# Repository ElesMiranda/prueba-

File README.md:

# prueba-
preuba del uso de kicad y Github

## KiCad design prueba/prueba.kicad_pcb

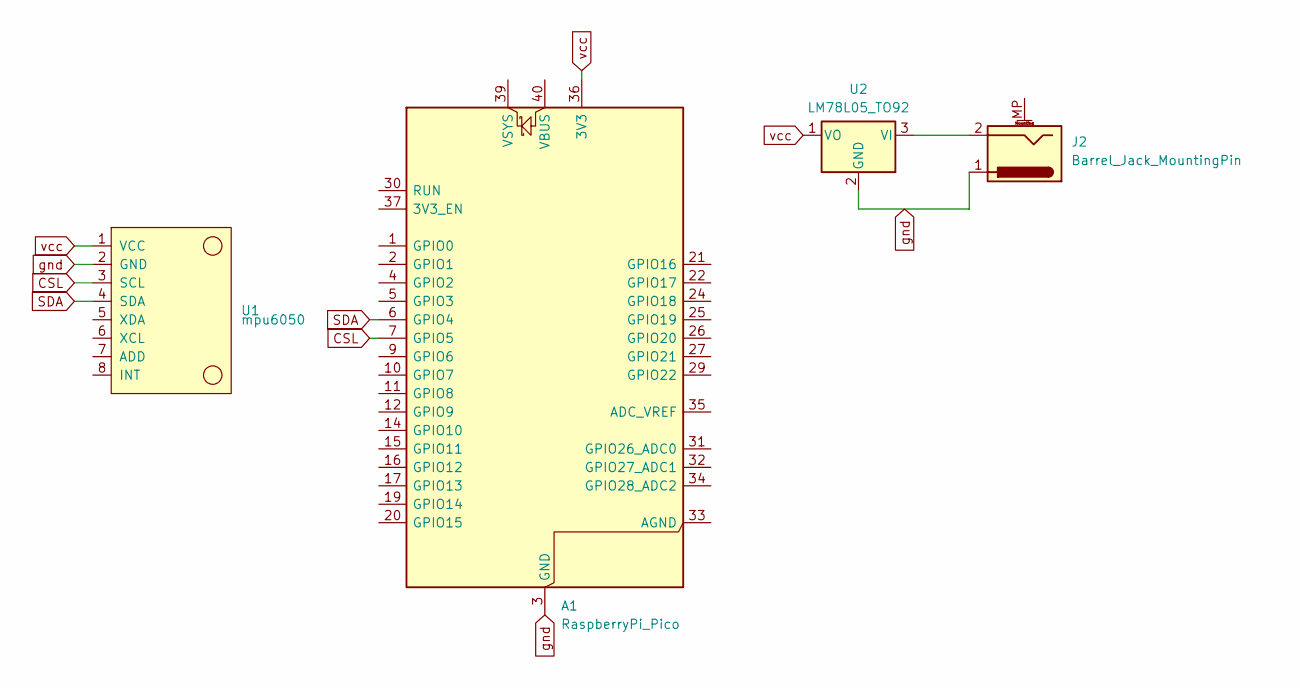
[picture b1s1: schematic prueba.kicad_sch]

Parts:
A1: RaspberryPi_Pico; RaspberryPi_Pico_Common_Unspecified
J2: Barrel_Jack_MountingPin; BarrelJack_GCT_DCJ200-10-A_Horizontal
U1: mpu6050; module_mpu6050
U2: LM78L05_TO92; TO-92

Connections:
CSL: A1.7 (GPIO5), U1.3 (SCL)
unnamed: J2.2, U2.3 (VI)
SDA: A1.6 (GPIO4), U1.4 (SDA)
gnd: A1.3 (GND), A1.8 (GND), A1.13 (GND), A1.18 (GND), A1.23 (GND), A1.28 (GND), A1.38 (GND), J2.1, U1.2 (GND), U2.2 (GND)
vcc: A1.36 (3V3), U1.1 (VCC), U2.1 (VO)

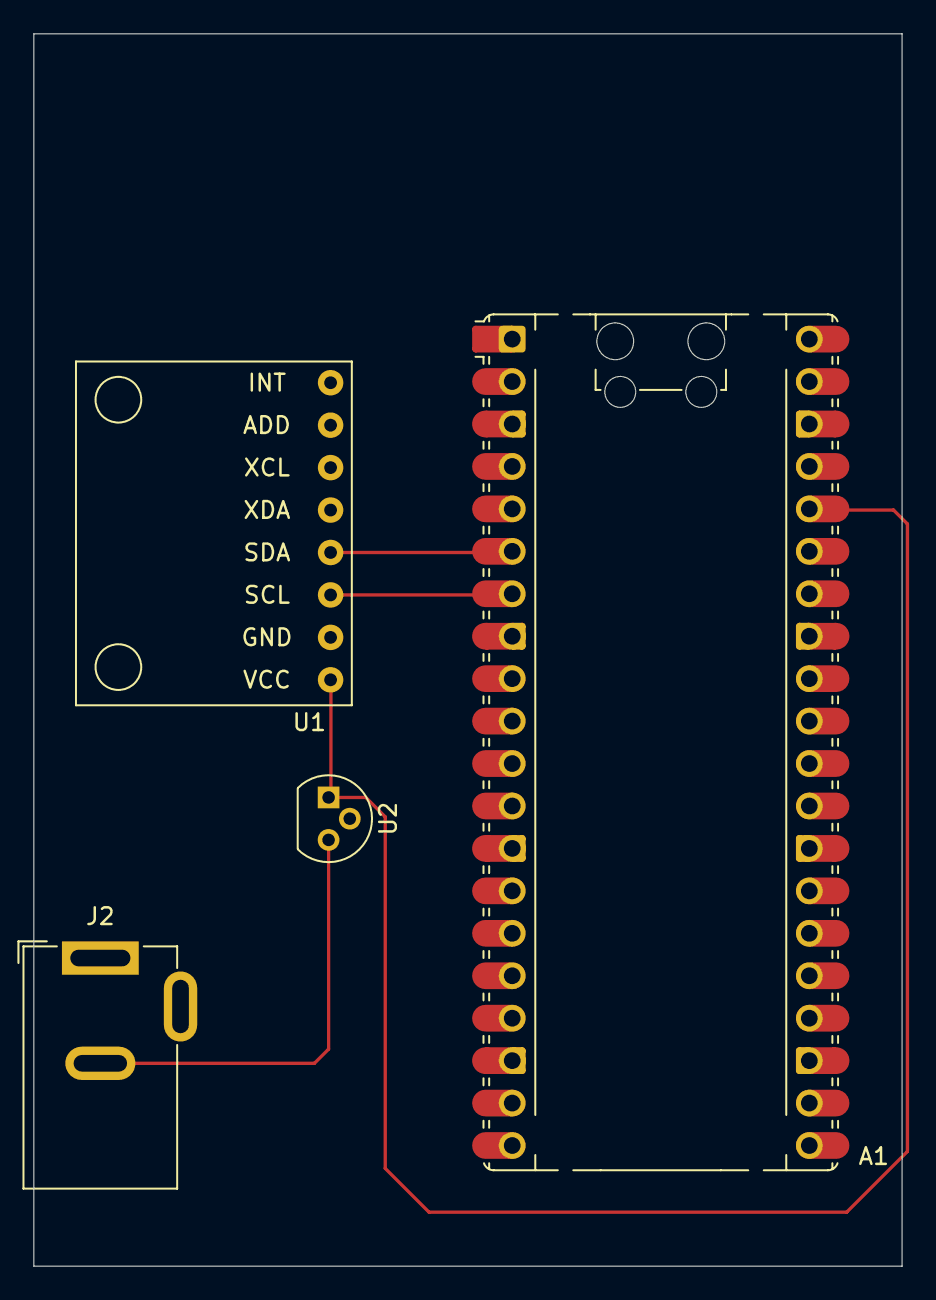
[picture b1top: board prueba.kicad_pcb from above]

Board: 2 copper layers, 52.0 x 73.8 mm, 4 parts (0 on the bottom side), 5 nets.

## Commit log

2026-04-01 add KiCad files
2026-04-01 first
2026-04-01 k hace
2026-04-01 eles
2026-04-01 topi
2026-04-01 eles2
2026-04-01 prueba random
2026-04-01 parael emi jaj
2026-04-01 resolver conflictos
